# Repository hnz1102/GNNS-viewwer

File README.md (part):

<div align="center">
  <h1><code>GNSS Satellite Viewer</code></h1>
  
</div>

ESP32-S3 firmware for a handheld GNSS receiver display built around a u-blox
**MAX-F10S** module.  It decodes the receiver's NMEA output and shows the fix,
satellite constellation, a live map and recorded tracks on a 320×240 colour TFT,
and serves the same data over Wi-Fi to a browser.  Written in
Rust (esp-idf-hal / esp-idf-svc) with a C component (wolfSSH) for an SSH
console to the receiver.

## Features

| Feature | Description |
|---------|-------------|
| GNSS status | Fix quality, position, altitude, speed, course, HDOP/VDOP, satellites used/in view, UTC time (GPS, Galileo, BeiDou, GLONASS, QZSS, NavIC as supported by the receiver) |
| Sky view | Polar plot of every tracked satellite by azimuth/elevation, coloured by constellation, with an SNR bar chart |
| Live map | Google Maps Static API tile (satellite or roadmap) centred on the current fix, with a position trail, crosshair and scale bar |
| Offline map cache | Every downloaded tile is cached on eMMC; the nearest cached tile is shown when Wi-Fi or the API key is unavailable |
| Track log | Fixes are logged to a daily CSV on eMMC and can be browsed and replayed on the map (see [Track playback](#track-playback)) |
| Reverse geocoding | Street address for the current position via OpenStreetMap Nominatim |
| Earthquakes / EEW | Optional (`quake_enable`): recent earthquakes and emergency earthquake warnings from P2P地震情報, shown on a TFT page, plotted on the map and listed in the Web UI (see [Earthquakes and EEW](#earthquakes-and-eew-p2p地震情報)) |
| Time sync | System time from the GNSS receiver, plus NTP (up to 4 servers) |
| Web UI | Browser-based configuration, map, sky view, GNSS status and serial terminal |
| SSH console | Transparent SSH access to the receiver's serial port (`ssh … console com1`) |
| WPS | Wi-Fi Protected Setup (PBC mode) via `cfg.toml` or the Web UI |
| UDP Syslog | RFC 5424 remote logging over UDP |
| NVS settings | Persistent configuration stored in NVS; editable via the Web UI at runtime |

---

## Hardware

The reference hardware is a custom board; the KiCad design files and
production data (BOM, placement, netlist) are in [`hw/`](hw/).

| Part | Notes |
|------|-------|
| MCU | ESP32-S3 with 16 MB flash and octal PSRAM |
| GNSS receiver | u-blox MAX-F10S on UART1 (COM1), 9600 baud default |
| Display | ST7789V 320×240 SPI TFT |
| Storage | **64 GB eMMC** on the 8-bit SDMMC bus, mounted at `/emmc` (map tile cache and track log) |
| Battery | **LiPo, 1100 mAh**, on a JST-PH 2-pin connector; MCP73831 charge controller on board.  Voltage is read on GPIO13 (see `adc_conversion_factor`) |
| 1PPS output | **Internal** 1PPS (time-pulse) output port from the MAX-F10S TIMEPULSE1 pin.  1 Hz by default; the frequency (disabled, 1 Hz … 10 MHz) is set under *GPS TIMEPULSE* in the Web UI configuration page, saved in NVS and re-applied to the receiver at every boot |
| RTC | 32.768 kHz crystal on GPIO15/16 |
| Buttons | BOOT (GPIO0) plus three user buttons (GPIO4/5/6) |

### Enclosure

The 3D-printable enclosure is in [`STL/`](STL/):

| File | Content |
|------|---------|
| [`upper.stl`](STL/upper.stl) | Upper case |
| [`bottom.stl`](STL/bottom.stl) | Bottom case |
| [`button.stl`](STL/button.stl) | Button |
| [`sw-cover.stl`](STL/sw-cover.stl) | Switch cover |
| [`GNSS-VIEWER.f3d`](STL/GNSS-VIEWER.f3d) | Fusion 360 design data (source of the STL files; open it in Autodesk Fusion to modify the enclosure and re-export) |

### Pin assignment

| Function | GPIO |
|----------|------|
| GNSS UART1 TX / RX | 42 / 41 (`com1_tx_pin` / `com1_rx_pin`) |
| TFT SCLK / MOSI / CS / DC / RST | 48 / 45 / 40 / 39 / 38 |
| eMMC CLK / CMD | 46 / 3 |
| eMMC D0–D7 | 47, 21, 10, 9, 17, 18, 8, 7 |
| Battery voltage (ADC) | 13 |
| Power-source detect | 1 (high = DC jack, low = USB) |
| Buttons | 0 (BOOT/Page), 4 (+), 5 (−), 6 (MAP mode) |

---

## Display Pages

The BOOT button cycles through the pages in this order:

| # | Page | Content |
|---|------|---------|
| 1 | GNSS | Fix info, position, location name and satellite SNR bar chart |
| 2 | SKY VIEW | Polar satellite plot and per-satellite panel |
| 3 | MAP | Live map with trail, or the track being replayed |
| 4 | SAVED TRACKS | List of recorded tracks |
| 5 | SERIAL [COM1] | Raw terminal view of the receiver's serial stream |
| 6 | SYSTEM INFO | IP address, SSID, RSSI, battery voltage, chip temperature, free heap, serial settings, firmware version and build date/time |
| 7 | EARTHQUAKE | Recent earthquakes (only with `quake_enable = "true"`) |

### Buttons

The button hint at the bottom of the MAP, SAVED TRACKS and EARTHQUAKE pages uses
the same symbols everywhere:

| GPIO | On-screen legend | Short press | Hold |
|------|------------------|-------------|------|
| 0 (BOOT) | yellow ● `PAGE` (`EXIT` during track playback or an alert) | Next page — or end track playback | ≥ 10 s: factory reset |
| 4 | blue `+UP` | Context dependent (below) | Auto-repeat |
| 5 | blue `-DOWN` | Context dependent (below) | Auto-repeat |
| 6 | red ● `TYPE` / `PLAY` / `MAP` | Toggle satellite ↔ roadmap (`TYPE`) — start playback on the track list (`PLAY`) — show the highlighted epicenter on the quake page (`MAP`) | — |

GPIO4/5 act as follows:

| Where | GPIO4 (UP, +) / GPIO5 (DOWN, −) |
|-------|----------------------|
| MAP page, live | Zoom in / out |
| MAP page, track playback | Next / previous point (×10 once the button auto-repeats) |
| SAVED TRACKS page | Move the highlight up / down |
| EARTHQUAKE page | Move the highlight up / down |

Buttons are debounced at 50 ms; auto-repeat starts after 400 ms and repeats
every 300 ms.

**Factory reset** — hold BOOT for 10 s.  From 6 s the display shows a
"FACTORY RESET" countdown; at 10 s it erases NVS, restores the `cfg.toml`
defaults and reboots.

### TFT screenshots

Samples of every page, rendered at 2× with synthetic data (Tokyo Tower area,
made-up satellites and earthquakes) and real Google Static Maps tiles.  They
are generated by [`tools/screenshots`](tools/screenshots/) — see
[Regenerating the TFT screenshots](#regenerating-the-tft-screenshots).

| | |
|---|---|
| <br>**GNSS** | <br>**SKY VIEW** |
| <br>**MAP** (roadmap) | <br>**MAP** (satellite) |
| <br>**MAP**, zoom ≤ 5: ground point under each satellite | <br>**SAVED TRACKS** |
| <br>**TRACK PLAYBACK** | <br>**SERIAL [COM1]** |
| <br>**SYSTEM INFO** | <br>**EARTHQUAKE** |
| <br>**MAP** framed on the selected quake | <br>**NEW QUAKE** on the MAP |
| <br>**EEW** alert | <br>System message overlay |
| <br>**GNSS**, no fix | <br>**EARTHQUAKE**, waiting for data |

---

## Track Playback

While a fix is valid, the position is logged at most once every 5 s to
`/emmc/tracks/YYYY-MM-DD.csv` (UTC date, one file per day):

```
time_utc,lat,lon,alt_m,speed_kn,course_deg,fix_quality,num_sats,hdop
```

To replay a track:

1. Press **BOOT** until the **SAVED TRACKS** page is shown (newest date first).
2. Use **+ / −** to highlight a day and press **MAP mode** to start.
3. For the first 5 seconds the map is zoomed out to show the **whole route** (yellow
   line) and the **end point** (`E`).  It then returns to your normal tracking
   scale, starting at the first point.
4. **+ / −** step through the recorded points — hold the button to move ten at a
   time.  The info bar shows the date, point number, time, altitude and speed.
5. Press **BOOT** to end playback and return to the live map.

Tracks can be deleted from the Web UI (Storage section).

### Browsing tracks in the Web UI

Open **Tracks** from the configuration page (or `http://<device_ip>/tracks`).
Pick a day from the drop-down; the whole route (yellow) is shown first with its
start (`S`) and end (`E`).  Use ◀ ▶ / ⏮ ⏭ (±1 / ±10 points), the slider, or the
arrow keys (Shift = ±10) to move through the points, or **Play** to replay at
1–20 points per second.  **Overview** keeps the whole route in view; **Follow**
(selected automatically by Play and by the zoom buttons) centres on the current
point at the zoom you choose.

The viewer runs in the browser and is independent of the device: it does not
change what the LCD is showing, and the LCD's track playback does not affect it.
Like the Map page, it loads the map image straight from Google using the
`maps_api_key` (without a key the route is still drawn, on a plain background).

---

## Earthquakes and EEW (P2P地震情報)

With `quake_enable = "true"` in `cfg.toml` (default `"false"`) the unit shows
recent earthquakes and emergency earthquake warnings (緊急地震速報, EEW) from
[P2P地震情報](https://www.p2pquake.net/) (JSON API v2).  The data is
originally issued by the Japan Meteorological Agency (気象庁).  It needs Wi-Fi
and a synced clock (GNSS or NTP), because the connection is TLS.

| Where | What you get |
|-------|--------------|
| **EARTHQUAKE** page (TFT, page 7) | The 8 most recent events: time (JST), magnitude, maximum intensity (`I5-` = 5弱, `I5+` = 5強, …), depth and epicenter coordinates; tsunami warnings are flagged.  **+ / −** move the highlight, **MAP mode** (GPIO6) shows the highlighted epicenter on the MAP page |
| **MAP** page | Epicenters of recent earthquakes inside the visible map are drawn as circles — sized by magnitude, coloured by maximum intensity — with a label such as `M5.2 I5-` |
| **Web UI** (configuration page) | A *Recent Earthquakes* card with the epicenter name (Japanese), magnitude, intensity, depth and tsunami status.  The epicenter name opens the Web UI map (`/map?lat=…&lon=…&zoom=…`) centred on it |
| **EEW alert** | On a warning the TFT switches to the MAP page by itself and frames the epicenter **and this unit's own position** at the largest zoom that shows both: the epicenter is a large red `X`, joined to your position by a line, the header turns red (`!! EEW M6.3 I5- !!`) and the info bar shows magnitude, maximum forecast intensity, depth and the distance in km.  The Web UI shows a red banner with the forecast areas and a link to the same map view.  The alert stays up for 2 minutes, or until it is cancelled or **BOOT** is pressed |

The TFT font is ASCII only, so Japanese epicenter and area names appear in the
Web UI only; the TFT shows coordinates.  Without a GNSS fix the alert still
shows the epicenter, but cannot mark your position or give a distance.

How it works (`src/quake.rs`):

- A WebSocket (`wss://api.p2pquake.net/v2/ws`) receives the events as they are
  registered.  Warnings (code 556) raise the alert, earthquake reports (551) are
  merged into the list.  Test messages and warnings older than 3 minutes (by
  their issue time) are ignored, so a boot in the middle of an old event does
  not alert.
- REST (`/v2/history`) loads the initial list at boot, re-syncs it every
  30 minutes, and takes over — polling every 10 s (EEW) / 60 s (list) — while
  the WebSocket is down.
- **Memory:** the TLS WebSocket holds roughly 30 KB of internal RAM, which
  competes with the map tile download.  The WebSocket is therefore dropped for
  the duration of every map fetch and re-created once the map has been idle for
  about 12 s; any warning issued in the gap is recovered by a REST check right
  after it reconnects.  REST polling is skipped while internal RAM is low or a
  map fetch is running.  Watch *Free Heap (Internal)* in the Web UI and
  `[HEAP]` / `[WS]` / `[QUAKE]` in the log.
- The WebSocket needs the `esp_websocket_client` ESP-IDF component, pulled from
  the component registry at build time (declared in `Cargo.toml`), so the first
  build needs network access.

**Testing without a real earthquake.**  Build with the sandbox feature:

```bash
cargo build --release --features quake-sandbox
```

This points the feed at the P2P sandbox, which replays old data (including a
2023 Hokkaido EEW) and skips the "older than 3 minutes" check, so the whole
alert path fires right after boot.  Never ship a sandbox build.

> **Not a safety device.**  Delivery is not guaranteed and can be delayed; the
> warning only covers what the Meteorological Agency issues as a warning.  Do
> not rely on this unit for life-safety decisions.  Use the official channels.
> Use of the data is subject to the P2P地震情報
> [terms for secondary use](https://www.p2pquake.net/secondary_use/): credit the
> Japan Meteorological Agency and P2P地震情報 (the Web UI card already does).

---

## Architecture

```
u-blox MAX-F10S ──[UART1 / COM1]──► usb_host.rs (serial bridge)
                                      ├── gps_parser.rs ──► GPS state (fix, sats)
                                      │     ├── track_log.rs ─► /emmc/tracks/*.csv
                                      │     └── geocoder.rs ──► address lookup
                                      ├── serial_display.rs (TFT task) ──► display_pages.rs (page drawing)
                                      ├── WebSocket terminal  (/terminal)
                                      └── ssh_bridge.c (wolfSSH, port 22)

map_display.rs ── persistent fetch worker ──► Google Static Maps (HTTPS)
      │                                         └── map_cache.rs ─► /emmc/mapcache
      └── MAP page / Web UI (/map)

track_view.rs ── track list + playback state for the MAP / SAVED TRACKS pages

quake.rs ── WebSocket (EEW + events) + REST ──► p2pquake.net   (quake_enable)
      └── EARTHQUAKE page / MAP overlay / EEW alert / Web UI card
```

---

## Directory Layout

```
satellite-viewer/
├── src/
│   ├── main.rs           # Entry point, peripheral initialisation
│   ├── usb_host.rs       # COM1 UART bridge to the GNSS receiver + SSH bridge control
│   ├── gps_parser.rs     # NMEA / UBX parser, GPS state, time sync
│   ├── serial_display.rs # ST7789V display task (SPI init, redraw loop)
│   ├── display_pages.rs  # Page drawing (GNSS, sky view, map, track list, terminal, info, earthquake); no ESP-IDF dependency
│   ├── map_display.rs    # Map tile fetch, JPEG decode, zoom, position trail
│   ├── map_cache.rs      # eMMC tile cache index and eviction
│   ├── track_log.rs      # Daily CSV track logging
│   ├── track_view.rs     # Track list and playback state
│   ├── geocoder.rs       # Reverse geocoding (Nominatim)
│   ├── quake.rs          # Earthquake list + EEW (P2P地震情報 WebSocket / REST)
│   ├── emmc.rs           # eMMC (SDMMC 8-bit) mount
│   ├── httpserver.rs     # HTTP/WebSocket server, NVS config management
│   ├── wifi.rs           # Wi-Fi STA connection (DHCP / static IP) and WPS
│   ├── syslogger.rs      # UDP Syslog logger (RFC 5424)
│   ├── btn_ctrl.rs       # Button handling
│   ├── boot_log.rs       # NVS boot counter and rolling reset-reason log (last 10 entries)
│   └── gpio_ctrl.rs      # Shared GPIO state
├── components/
│   ├── ssh_bridge/       # SSH server C component (wolfSSH wrapper)
│   ├── wolfssh/          # wolfSSH (github.com/wolfSSL/wolfssh, commit 157cb01f)
│   └── wolfssl/          # wolfSSL/wolfCrypt (github.com/wolfSSL/wolfssl, commit b7e7e755)
├── tools/
│   └── screenshots/      # Host tool: renders every TFT page to PNG (see below)
├── docs/images/          # README images; tft/ holds the generated TFT screenshots
├── hw/                   # KiCad schematic/PCB and production files
├── STL/                  # Enclosure: STL files for 3D printing + Fusion 360 data (GNSS-VIEWER.f3d)
├── static/               # Embedded static files (xterm.js / css / fit addon)
├── cfg.toml              # Build-time default configuration (gitignored — contains credentials)
├── cfg.toml.tmp          # Template for cfg.toml (safe to commit)
├── sdkconfig.defaults    # ESP-IDF build settings
├── partitions.csv        # Flash partition table
├── setup_components.sh   # Initial setup script for components/
├── setup_env.sh          # One-shot environment setup (Rust, espup, udev)
└── build-flash-images.sh # Build merged flash images (quake_enable off / on) from the cfg.toml.tmp defaults
```

---

## Configuration

### cfg.toml (build-time defaults)

`cfg.toml.tmp` is the only template.  Before building, copy it to `cfg.toml`
(which is not committed, since it holds your Wi-Fi credentials and API key):

```bash
cp cfg.toml.tmp cfg.toml
```

Then edit `cfg.toml` for your environment.  The table name must match the crate
name, `[satellite-viewer]`, or the values are ignored.  Hardware variants are
selected with the settings below rather than separate templates:

| Setting | Default | Change it when |
|---------|---------|----------------|
| `com1_tx_pin` / `com1_rx_pin` | `42` / `41` | The GNSS receiver is wired to other pins (XIAO ESP32S3: `43` / `44`) |
| `display_enable` | `"true"` | There is no ST7789V TFT |
| `emmc_enable` | `"true"` | This unit has no eMMC fitted |
| `quake_enable` | `"false"` | You want the recent-earthquake list and **EEW** (緊急地震速報, emergency earthquake warning) alerts from P2P地震情報.  Off by default: it keeps a TLS WebSocket open (~30 KB of internal RAM) and needs Wi-Fi plus a synced clock.  Read at boot only, so rebuild after changing it — see [Earthquakes and EEW](#earthquakes-and-eew-p2p地震情報) |

```toml
[satellite-viewer]
wps_enable     = "true"     # "true": use WPS PBC on next boot when SSID is empty
wifi_ssid      = ""         # your-ssid
wifi_psk       = ""         # your-password
ip_mode        = "dhcp"           # "dhcp" or "static"
ip_address     = "192.168.0.200"
subnet_mask    = "255.255.255.0"
gateway        = "192.168.0.1"
dns            = "1.1.1.1"

syslog_server    = "192.168.0.140:514"
syslog_enable    = "false"
syslog_host_name = "esp32s3"
syslog_app_name  = "satellite-viewer"

ssh_user     = "admin"
ssh_password = "sshpass"

com1_tx_pin = "42"
com1_rx_pin = "41"
com1_baud   = "9600"

display_enable = "true"
display_port   = "com1"    # "com1"

ntp_server1 = "time.aws.com"
ntp_server2 = "time.google.com"
ntp_server3 = "time.cloudflare.com"
ntp_server4 = "ntp.nict.jp"

adc_conversion_factor = "437.98"

emmc_enable          = "true"    # "false": this unit has no eMMC chip populated — skip mount, avoids the SDMMC-failure-induced reset

# P2P地震情報 (p2pquake.net) feed: recent earthquakes + emergency earthquake warnings (EEW).
# "true": enable. Default "false" — it keeps a TLS WebSocket open (~30 KB of internal RAM)
# and needs WiFi plus a synced clock. Data: JMA via P2P地震情報.
quake_enable         = "false"

# Google Maps Static API key — get one at https://console.cloud.google.com/ (enable "Maps Static API", see README).
# This is only the default: the key can also be entered in the Web UI (Config > Map Settings), which overrides it.
# Never commit a real key here; put it in your local, uncommitted cfg.toml, or leave it unset and use the Web UI.
maps_api_key = ""
```

Values in `cfg.toml` are compiled into the firmware as defaults.
After boot they can be overridden via the Web UI or direct NVS writes; NVS values take priority.

### Google Maps API key

The map pages (LCD and Web UI) download images from the **Maps Static API**, so
they need a Google Maps Platform API key.  Without `maps_api_key` the MAP page
can still display tiles already stored in the eMMC cache, but will not download
new ones.

**Where to get one**

1. Sign in to the [Google Cloud console](https://console.cloud.google.com/) and
   create (or select) a project.
2. Link a **billing account** to the project.  Maps Platform APIs require one,
   even though usage within the free monthly allowance is not charged — see the
   [Google Maps Platform pricing](https://mapsplatform.google.com/pricing/) page
   for the current allowance.
3. Open **APIs & Services → Library**, search for **Maps Static API** and click
   **Enable**.
4. Open **APIs & Services → Credentials**, click **Create credentials → API key**
   and copy the key.  Step-by-step instructions are in Google's
   [Maps Static API documentation](https://developers.google.com/maps/documentation/maps-static/get-api-key).
5. Enter the key in the Web UI: **Config page → Map Settings → Google Maps API
   Key**, then **Save**.  It takes effect immediately (no reboot) and is stored
   in NVS.  To have a key built in as the default instead (for a fresh or
   factory-reset device), set it in `cfg.toml` and rebuild:

   ```toml
   maps_api_key = "your-api-key"
   ```

**Notes**

- The key is stored in NVS and can be changed from the Web UI at any time.
  `maps_api_key` in `cfg.toml` is only the default, used until a key is saved
  and restored by a factory reset (saving an empty field also falls back to it).
- The Web UI map pages load images directly from Google in your browser, so the
  device hands the key to any logged-in browser (`/api/mapkey`).  Keep the
  device login password strong, and do not share firmware images built with your
  own key (`build-flash-images.sh` builds from `cfg.toml.tmp`, whose key is empty).
- In the Cloud console, restrict the key under **API restrictions** to the
  **Maps Static API** only, and set a budget alert or quota so a leaked key cannot
  run up a bill.  An application restriction (HTTP referrer / IP) is awkward here
  because requests come both from the device and from browsers on your LAN.
- `cfg.toml` is not committed.  Never put a real key in `cfg.toml.tmp`, which is
  the template that gets committed.  Because the Web UI can set the key, you can
  leave `cfg.toml` empty and keep the key out of the build entirely.

---

## Wi-Fi Setup with WPS

**WPS (Wi-Fi Protected Setup)** allows you to connect to a Wi-Fi network without manually entering the SSID and password. This device supports **WPS Push Button Configuration (PBC)** mode.

### Method 1: Using cfg.toml and Factory Reset (Recommended for initial setup)

If you don't have Wi-Fi credentials yet or want to reconfigure via WPS without Web UI access:

1. **Edit `cfg.toml` before building** (or rebuild the firmware):
   ```toml
   wifi_ssid      = ""           # Set to empty string
   wps_enable     = "true"       # Enable WPS mode on boot
   ```

2. **Flash the firmware** to the device

3. On boot, the device will automatically enter WPS mode and wait for you to **press the WPS button on your Wi-Fi router** (timeout: 2 minutes)

4. Upon successful WPS connection, the credentials are saved to NVS and the device reboots

**Alternative: Trigger WPS via Factory Reset**

If the device is already running with Wi-Fi configured but you want to switch to WPS:

1. **Edit `cfg.toml`** to set `wps_enable = "true"` and `wifi_ssid = ""`
2. **Rebuild and flash** the firmware
3. **Perform a Factory Reset**: Press and hold the BOOT button (GPIO 0) for **≥10 seconds**
4. The device will erase NVS, restore `cfg.toml` defaults, and reboot into WPS mode
5. **Press the WPS button on your Wi-Fi router** within 2 minutes

> **Note**: Web UI is not accessible until Wi-Fi is connected, so this method is essential for initial setup or when you lose Wi-Fi access.

### Method 2: Using the Web UI (when already connected to Wi-Fi)

1. Navigate to the configuration page at `http://<device_ip>/`
2. Find the **WPS** section
3. Click the **"Start WPS"** button
4. **Press the WPS button on your Wi-Fi router** within 2 minutes
5. The device will automatically receive and save the Wi-Fi credentials and reboot

### WPS Fallback

If WPS fails or times out, the device will revert to the previously configured Wi-Fi credentials (from `cfg.toml` or NVS).

### Notes

- WPS PBC mode is the only supported WPS method (PIN mode is not supported)
- After successful WPS configuration, the new credentials are saved to NVS and persist across reboots
- You can still manually configure Wi-Fi credentials via `cfg.toml` or the Web UI if WPS is not available on your router

---

## Environment Setup

Run `setup_env.sh` **once** on a fresh Ubuntu / Debian machine (or WSL2) before
building.  The script performs all steps below automatically.

```bash
bash setup_env.sh
```

After the script finishes, open a new terminal (or reload your shell config) so
the environment variables take effect:

```bash
source "$HOME/.cargo/env"
source ~/export-esp.sh
```

### What the script does

| Step | Action |
|------|--------|
| 1 | Install system packages via `apt` |
| 2 | Install Rust toolchain via `rustup` (skipped if already present) |
| 3 | Install `ldproxy`, `espup`, `cargo-espflash` via Cargo |
| 4 | Install & update the ESP32-S3 Xtensa toolchain via `espup` |
| 5 | Source `~/export-esp.sh` (generated by `espup`) |
| 6 | Add udev rule for ESP32 USB device (`303a:1001`) and reload rules |

> If you prefer to run the steps manually, expand the section below.

<details>
<summary>Manual setup steps</summary>

```bash
# 1. System packages
sudo apt update && sudo apt -y install \
    git python3 python3-pip gcc build-essential curl \
    pkg-config libudev-dev libtinfo5 clang libclang-dev \
    llvm-dev udev libssl-dev python3.10-venv

# 2. Rust
curl --proto '=https' --tlsv1.2 -sSf https://sh.rustup.rs | sh
# Select option 1 (default install), then:
source "$HOME/.cargo/env"

# 3. Cargo tools
cargo install ldproxy
cargo install espup
cargo install cargo-espflash

# 4. ESP32-S3 toolchain
espup install
espup update

# 5. Activate ESP environment (add to ~/.bashrc / ~/.zshrc for persistence)
. ~/export-esp.sh

# 6. udev rules
sudo sh -c 'echo "SUBSYSTEMS==\"usb\", ATTRS{idVendor}==\"303a\", ATTRS{idProduct}==\"1001\", MODE=\"0666\"" > /etc/udev/rules.d/99-esp32.rules'
sudo udevadm control --reload-rules
sudo udevadm trigger
```

</details>

---

## Build and Flash

### Prerequisites

- Rust toolchain: `esp` channel (selected automatically via `rust-toolchain.toml`)
- [espup](https://github.com/esp-rs/espup) — ESP32-S3 Xtensa toolchain
- [espflash](https://github.com/esp-rs/espflash)
- ESP-IDF v5.4.2 (fetched automatically by the build)

### Initial component setup

Run once after cloning, or after a clean wipe of `components/`:

```bash
cd esp32-s3/satellite-viewer
bash setup_components.sh
```

This clones wolfssh and wolfssl at the verified commits, places the
ESP-IDF-specific `CMakeLists.txt` and `include/user_settings.h` on top, and
patches the FAT filesystem configuration to enable exFAT for the eMMC.

### Build

```bash
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
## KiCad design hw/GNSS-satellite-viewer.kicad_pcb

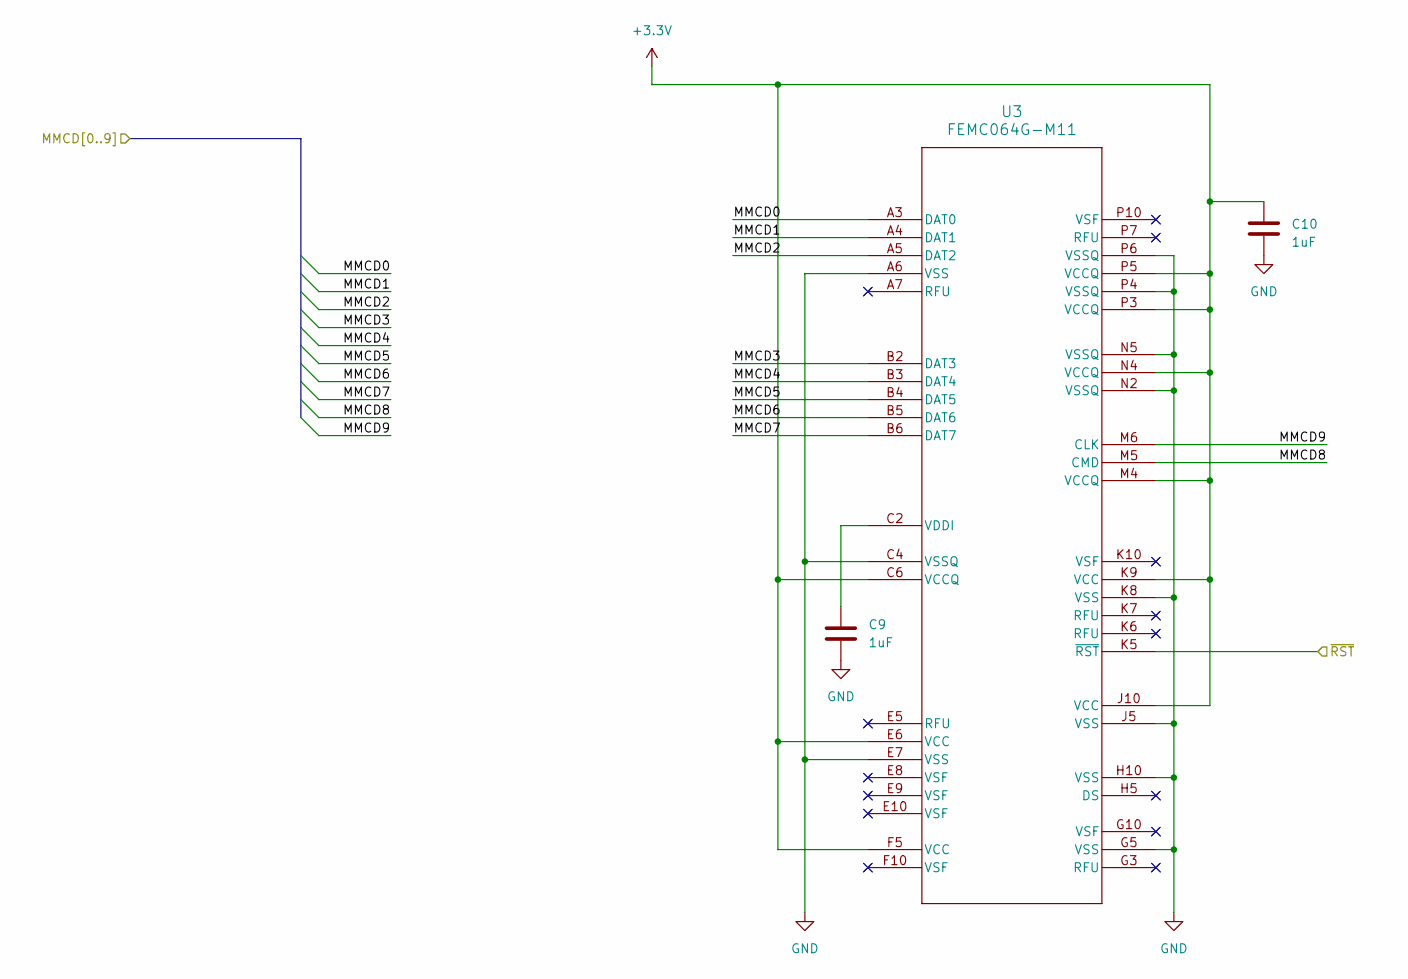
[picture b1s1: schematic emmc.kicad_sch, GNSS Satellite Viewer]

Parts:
C9, C10: 1uF; C_0805_2012Metric; digikey 1276-1026-1-ND
U3: FEMC064G-M11; EM32VSUKN FPGA153; digikey 3052-FEMC064G-M11-ND

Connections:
+3.3V: C10.1, U3.C6 (VCCQ), U3.E6 (VCC), U3.F5 (VCC), U3.J10 (VCC), U3.K9 (VCC), U3.M4 (VCCQ), U3.N4 (VCCQ), U3.P3 (VCCQ), U3.P5 (VCCQ); also elsewhere on the board
/MPU/MMCD0: U3.A3 (DAT0); also elsewhere on the board
/MPU/MMCD1: U3.A4 (DAT1); also elsewhere on the board
/MPU/MMCD2: U3.A5 (DAT2); also elsewhere on the board
/MPU/MMCD3: U3.B2 (DAT3); also elsewhere on the board
/MPU/MMCD4: U3.B3 (DAT4); also elsewhere on the board
/MPU/MMCD5: U3.B4 (DAT5); also elsewhere on the board
/MPU/MMCD6: U3.B5 (DAT6); also elsewhere on the board
/MPU/MMCD7: U3.B6 (DAT7); also elsewhere on the board
/MPU/MMCD8: U3.M5 (CMD); also elsewhere on the board
/MPU/MMCD9: U3.M6 (CLK); also elsewhere on the board
/MPU/~RESET: U3.K5 (~RST); also elsewhere on the board
GND: C9.2, C10.2, U3.A6 (VSS), U3.C4 (VSSQ), U3.E7 (VSS), U3.G5 (VSS), U3.H10 (VSS), U3.J5 (VSS), U3.K8 (VSS), U3.N2 (VSSQ), U3.N5 (VSSQ), U3.P4 (VSSQ), U3.P6 (VSSQ); also elsewhere on the board
unnamed: C9.1, U3.C2 (VDDI)

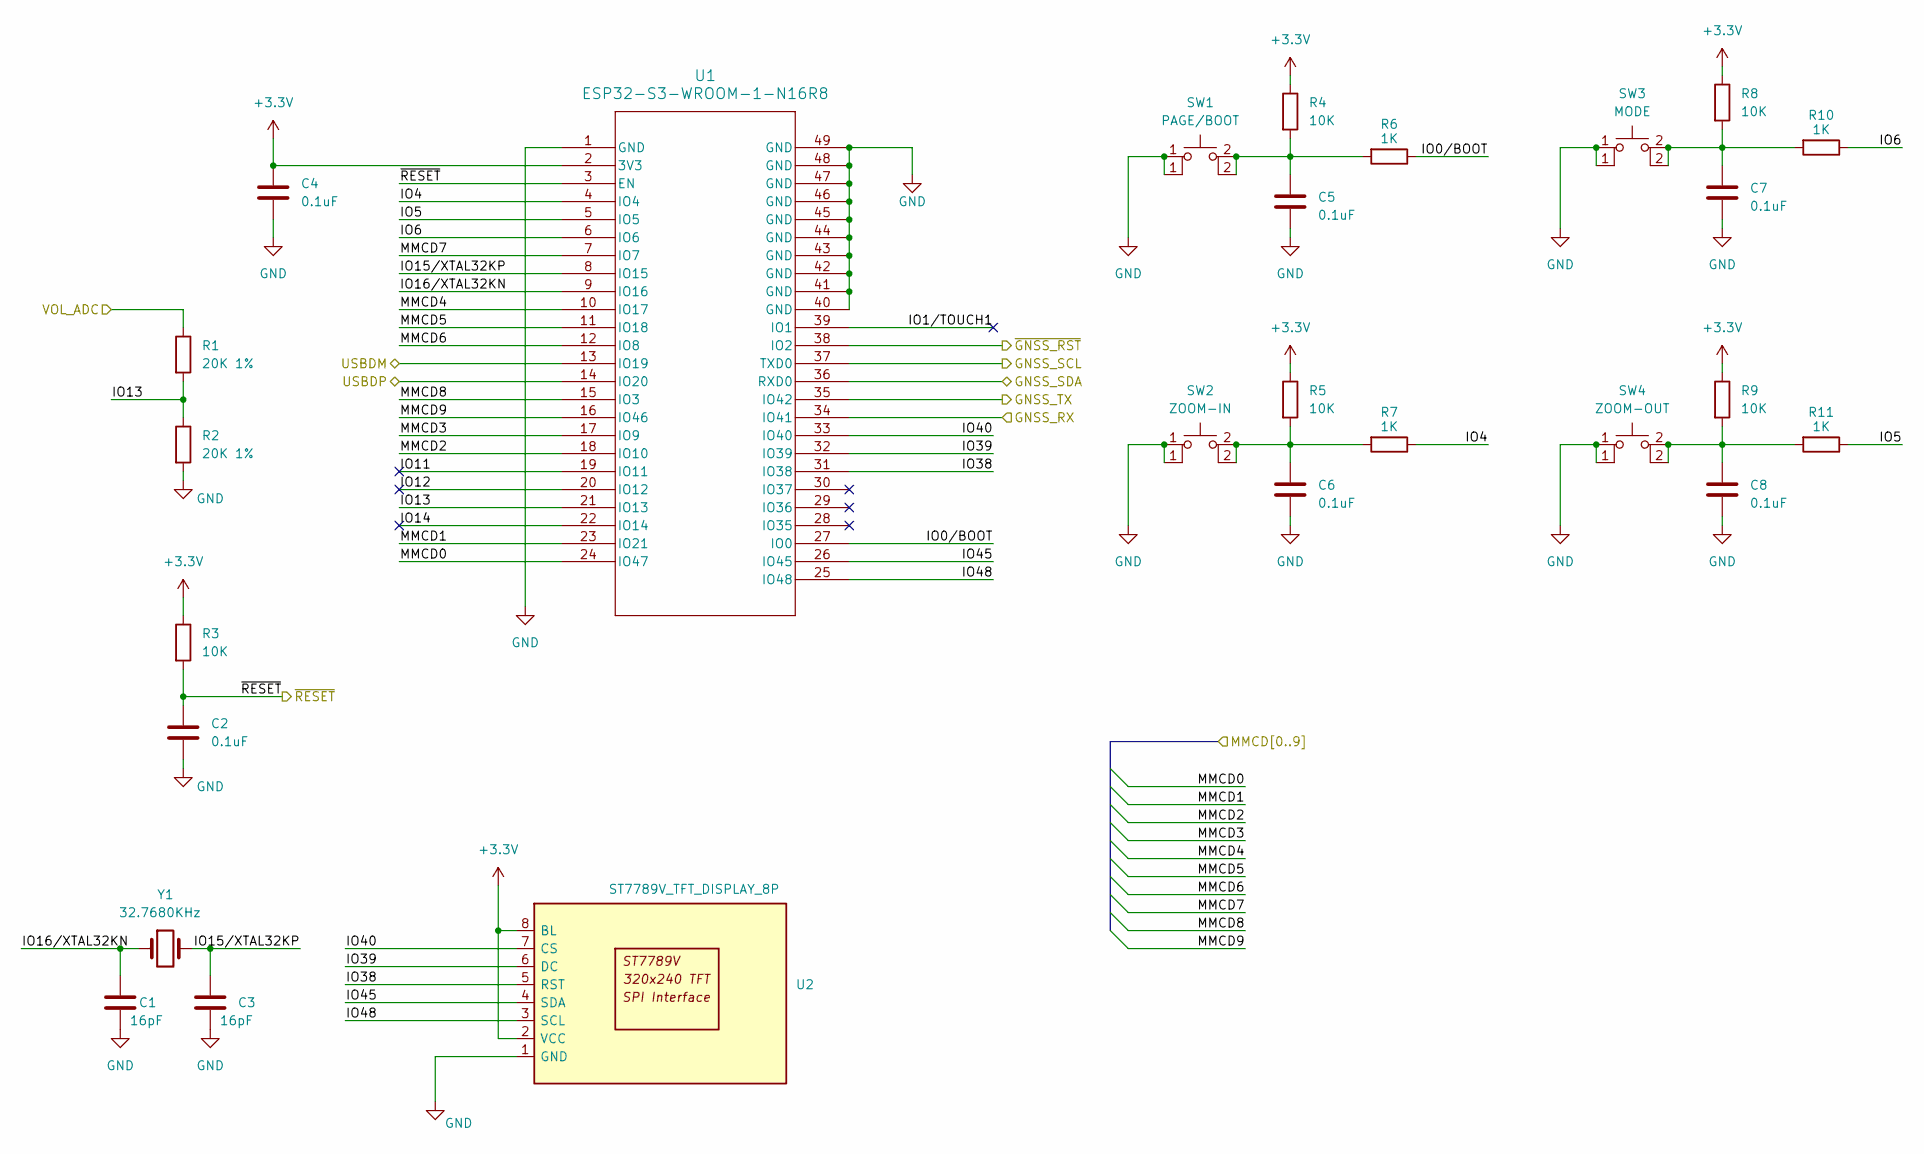
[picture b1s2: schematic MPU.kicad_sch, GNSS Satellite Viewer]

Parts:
C1, C3: 16pF; C_0603_1608Metric; digikey 1292-1490-1-ND
C2, C4, C5, C6, C7, C8: 0.1uF; C_0603_1608Metric; digikey 311-1344-1-ND
R1, R2: 20K 1%; R_0603_1608Metric; digikey 311-20.0KHRCT-ND
R3, R4, R5, R8, R9: 10K; R_0603_1608Metric; digikey 13-RC0603JR-1010KLCT-ND
R6, R7, R10, R11: 1K; R_0603_1608Metric; digikey 311-1.00KHRCT-ND
SW1: PAGE/BOOT; SW_PUSH_6mm_H8mm; digikey 2223-TS02-66-70-BK-160-LCR-D-ND
SW2: ZOOM-IN; SW_PUSH_6mm_H8mm; digikey 2223-TS02-66-70-BK-160-LCR-D-ND
SW3: MODE; SW_PUSH_6mm_H8mm; digikey 2223-TS02-66-70-BK-160-LCR-D-ND
SW4: ZOOM-OUT; SW_PUSH_6mm_H8mm; digikey 2223-TS02-66-70-BK-160-LCR-D-ND
U1: ESP32-S3-WROOM-1-N16R8; ESP32-S3-WROOM-1_EXP; digikey 1965-ESP32-S3-WROOM-1-N16R8CT-ND
U2: ST7789V_TFT_DISPLAY_8P; ST7789V TFT SPI DISPLAY 320x240 GMT020-02-8P; digikey GMT020-02-8P
Y1: 32.7680KHz; Crystal_SMD_3215-2Pin_3.2x1.5mm; digikey 2151-RT3215-32.768-12.5-TRCT-ND

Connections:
+3.3V: C4.1, R3.1, R4.1, R5.1, R8.1, R9.1, U1.2 (3V3), U2.2 (VCC), U2.8 (BL); also elsewhere on the board
/GNSS-RF/GNSS_RX: U1.35 (IO42); also elsewhere on the board
/GNSS-RF/GNSS_SCL: U1.37 (TXD0); also elsewhere on the board
/GNSS-RF/GNSS_SDA: U1.36 (RXD0); also elsewhere on the board
/GNSS-RF/GNSS_TX: U1.34 (IO41); also elsewhere on the board
/GNSS-RF/~GNSS_RST: U1.38 (IO2); also elsewhere on the board
/MPU/IO0/BOOT: R6.1, U1.27 (IO0)
/MPU/IO1/TOUCH1: U1.39 (IO1)
/MPU/IO4: R7.1, U1.4 (IO4)
/MPU/IO5: R11.1, U1.5 (IO5)
/MPU/IO6: R10.1, U1.6 (IO6)
/MPU/IO11: U1.19 (IO11)
/MPU/IO12: U1.20 (IO12)
/MPU/IO13: R1.2, R2.1, U1.21 (IO13)
/MPU/IO14: U1.22 (IO14)
/MPU/IO15/XTAL32KP: C3.1, U1.8 (IO15), Y1.2
/MPU/IO16/XTAL32KN: C1.1, U1.9 (IO16), Y1.1
/MPU/IO38: U1.31 (IO38), U2.5 (RST)
/MPU/IO39: U1.32 (IO39), U2.6 (DC)
/MPU/IO40: U1.33 (IO40), U2.7 (CS)
/MPU/IO45: U1.26 (IO45), U2.4 (SDA)
/MPU/IO48: U1.25 (IO48), U2.3 (SCL)
/MPU/MMCD0: U1.24 (IO47); also elsewhere on the board
/MPU/MMCD1: U1.23 (IO21); also elsewhere on the board
/MPU/MMCD2: U1.18 (IO10); also elsewhere on the board
/MPU/MMCD3: U1.17 (IO9); also elsewhere on the board
/MPU/MMCD4: U1.10 (IO17); also elsewhere on the board
/MPU/MMCD5: U1.11 (IO18); also elsewhere on the board
/MPU/MMCD6: U1.12 (IO8); also elsewhere on the board
/MPU/MMCD7: U1.7 (IO7); also elsewhere on the board
/MPU/MMCD8: U1.15 (IO3); also elsewhere on the board
/MPU/MMCD9: U1.16 (IO46); also elsewhere on the board
/MPU/USBDM: U1.13 (IO19); also elsewhere on the board
/MPU/USBDP: U1.14 (IO20); also elsewhere on the board
/MPU/~RESET: C2.1, R3.2, U1.3 (EN); also elsewhere on the board
/power/VOUT: R1.1; also elsewhere on the board
GND: C1.2, C2.2, C3.2, C4.2, C5.2, C6.2, C7.2, C8.2, R2.2, SW1.1, SW2.1, SW3.1, SW4.1, U1.1 (GND), U1.40 (GND), U1.41 (GND), U1.42 (GND), U1.43 (GND), U1.44 (GND), U1.45 (GND), U1.46 (GND), U1.47 (GND), U1.48 (GND), U1.49 (GND), U2.1 (GND); also elsewhere on the board
unnamed: C5.1, R4.2, R6.2, SW1.2
unnamed: C6.1, R5.2, R7.2, SW2.2
unnamed: C7.1, R8.2, R10.2, SW3.2
unnamed: C8.1, R9.2, R11.2, SW4.2

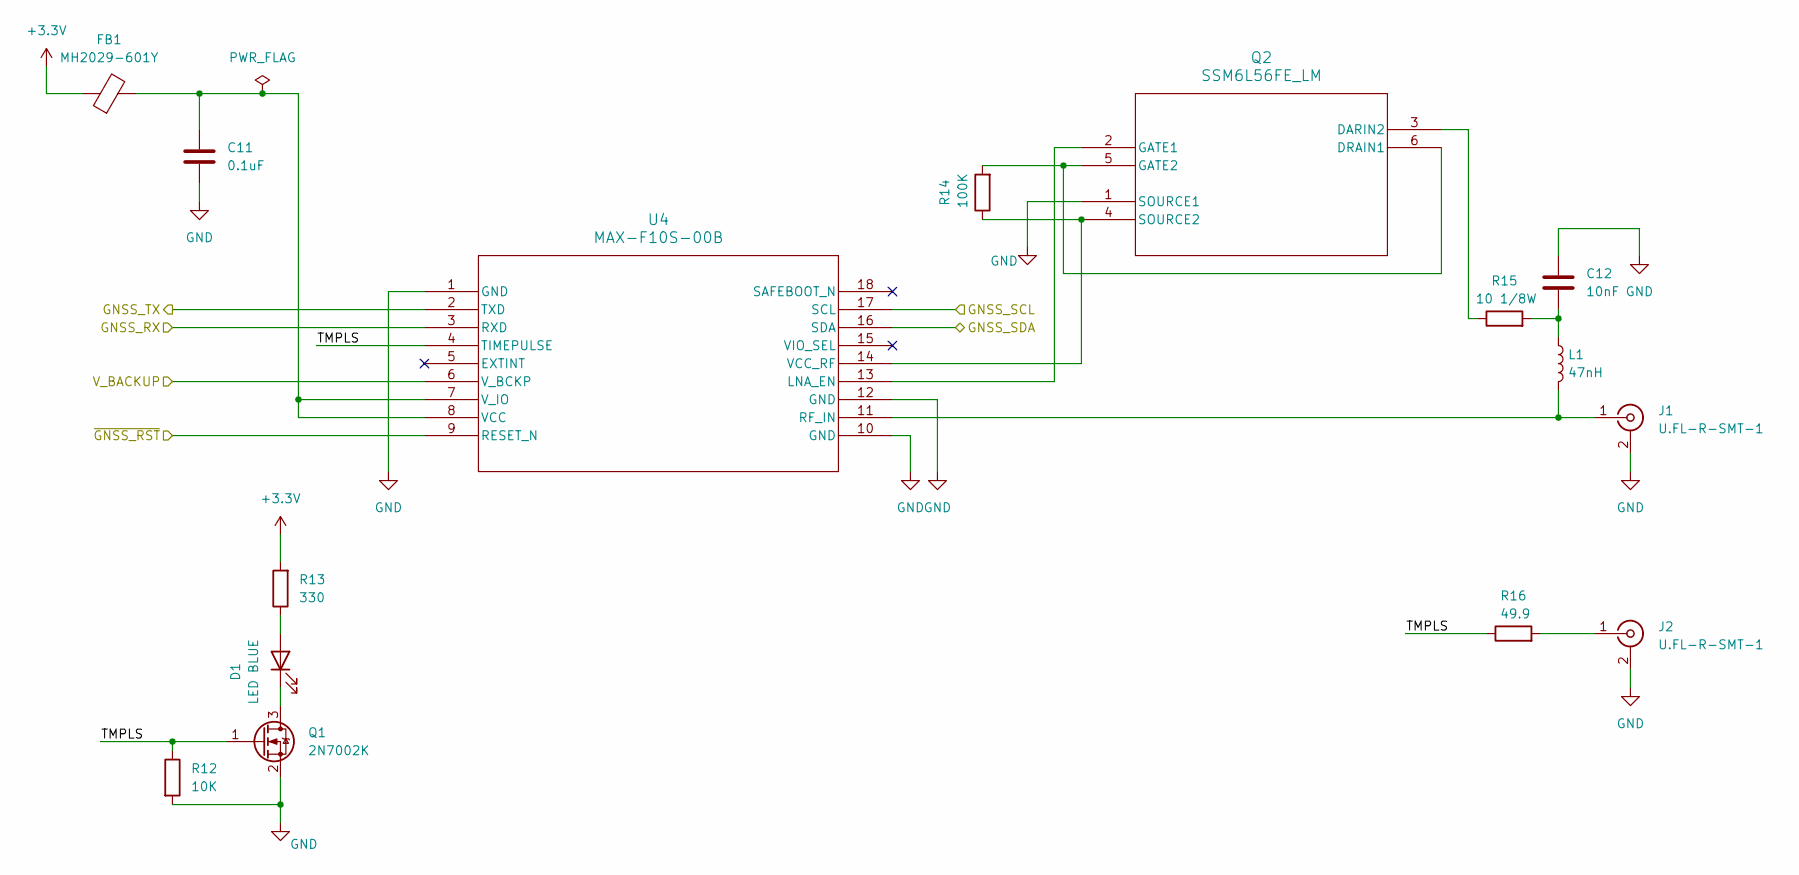
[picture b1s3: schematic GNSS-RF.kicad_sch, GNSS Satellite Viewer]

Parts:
C11: 0.1uF; C_0603_1608Metric; digikey 311-1344-1-ND
C12: 10nF; C_0603_1608Metric; digikey 311-1085-1-ND
D1: LED BLUE; LED_0603_1608Metric; digikey 3147-B1931NB--20C007614U1930CT-ND
FB1: MH2029-601Y; L_0805_2012Metric; digikey MH2029-601YCT-ND
J1, J2: U.FL-R-SMT-1; U.FL_Hirose_U.FL-R-SMT-1_Vertical; digikey 26-U.FL-R-SMT-1(80)CT-ND
L1: 47nH; L_0603_1608Metric; digikey 490-6582-1-ND
Q1: 2N7002K; SOT-23; digikey 5399-2N7002KCT-ND
Q2: SSM6L56FE_LM; SOT-563ES6_TOS; digikey 264-SSM6L56FELMCT-ND
R12: 10K; R_0603_1608Metric; digikey 13-RC0603JR-1010KLCT-ND
R13: 330; R_0603_1608Metric; digikey 13-RC0603JR-13330RLCT-ND
R14: 100K; R_0603_1608Metric; digikey 311-100KGRCT-ND
R15: 10 1/8W; R_0805_2012Metric; digikey 541-10.0CCT-ND
R16: 49.9; R_0603_1608Metric; digikey 311-49.9HRCT-ND
U4: MAX-F10S-00B; MAX-F10S_UBL; digikey 672-MAX-F10S-00BCT-ND

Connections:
+3.3V: FB1.1, R13.2; also elsewhere on the board
/GNSS-RF/GNSS_RX: U4.3 (RXD); also elsewhere on the board
/GNSS-RF/GNSS_SCL: U4.17 (SCL); also elsewhere on the board
/GNSS-RF/GNSS_SDA: U4.16 (SDA); also elsewhere on the board
/GNSS-RF/GNSS_TX: U4.2 (TXD); also elsewhere on the board
/GNSS-RF/TMPLS: Q1.1 (G), R12.1, R16.1, U4.4 (TIMEPULSE)
/GNSS-RF/V_BACKUP: U4.6 (V_BCKP); also elsewhere on the board
/GNSS-RF/~GNSS_RST: U4.9 (RESET_N); also elsewhere on the board
GND: C11.2, C12.1, J1.2 (Ext), J2.2 (Ext), Q1.2 (S), Q2.1 (SOURCE1), R12.2, U4.1 (GND), U4.10 (GND), U4.12 (GND); also elsewhere on the board
unnamed: C12.2, L1.1, R15.2
unnamed: D1.2 (A), R13.1
unnamed: D1.1 (K), Q1.3 (D)
unnamed: J1.1 (In), L1.2, U4.11 (RF_IN)
unnamed: J2.1 (In), R16.2
unnamed: Q2.3 (DARIN2), R15.1
unnamed: Q2.5 (GATE2), Q2.6 (DRAIN1), R14.2
unnamed: Q2.2 (GATE1), U4.13 (LNA_EN)
unnamed: Q2.4 (SOURCE2), R14.1, U4.14 (VCC_RF)
unnamed: C11.1, FB1.2, U4.7 (V_IO), U4.8 (VCC)

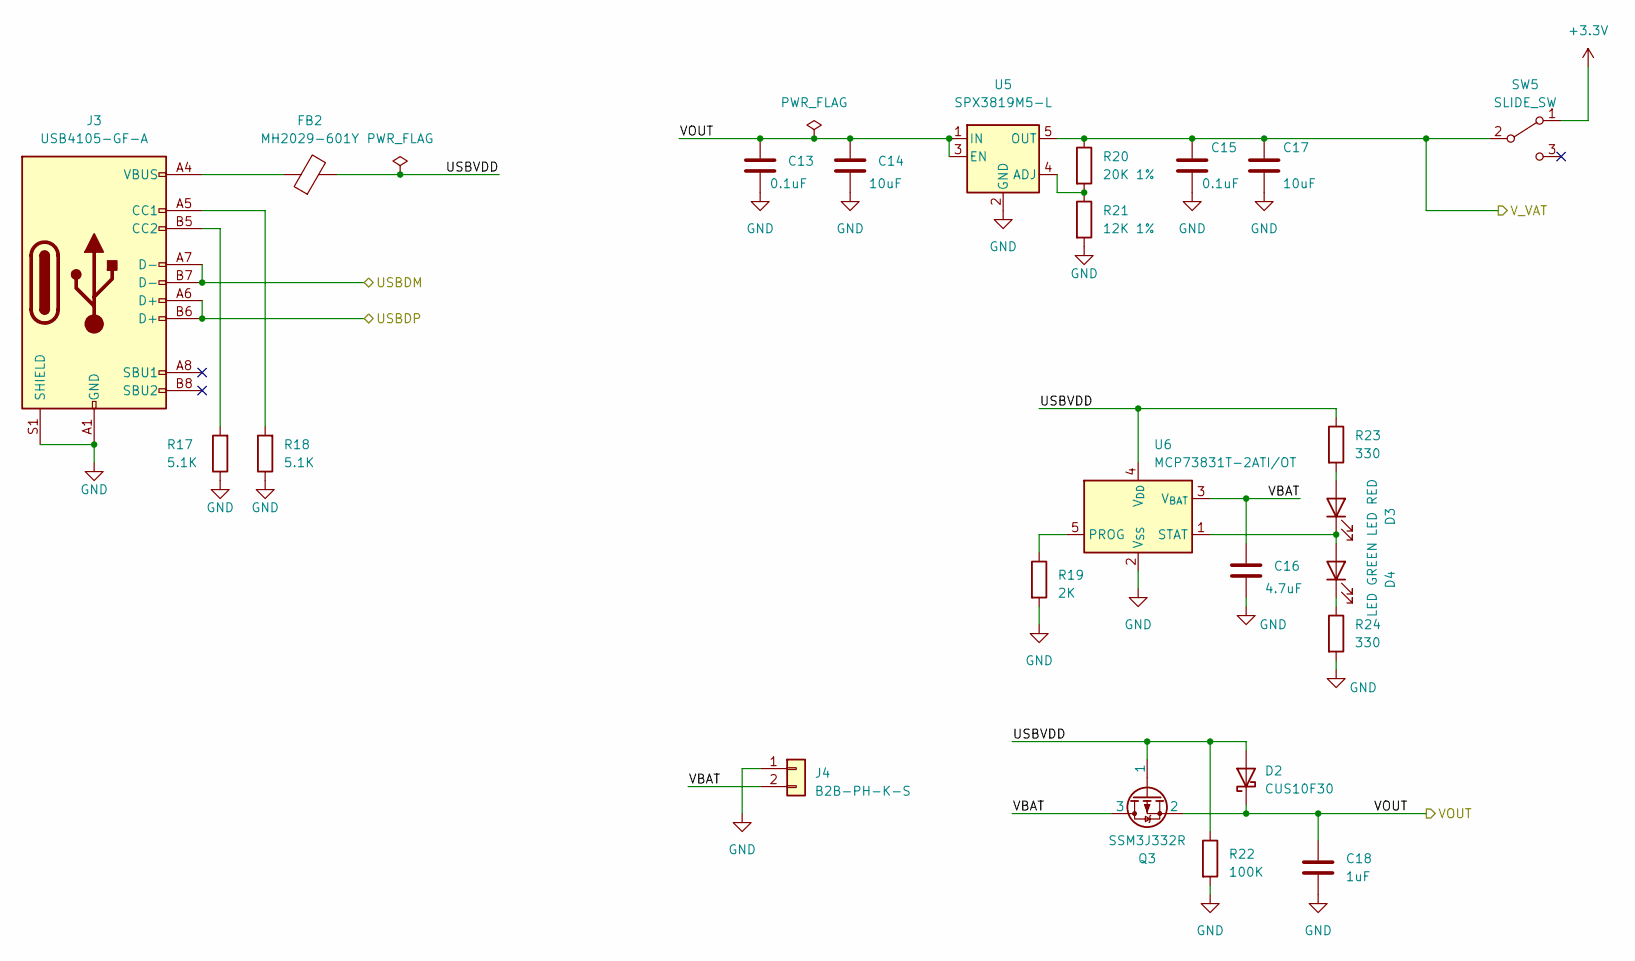
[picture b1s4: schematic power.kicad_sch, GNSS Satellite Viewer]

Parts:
C13, C15: 0.1uF; C_0603_1608Metric; digikey 311-1344-1-ND
C14, C17: 10uF; C_0805_2012Metric; digikey 1276-1096-1-ND
C16: 4.7uF; C_0805_2012Metric; digikey 1276-1244-1-ND
C18: 1uF; C_0805_2012Metric; digikey 1276-1026-1-ND
D2: CUS10F30; D_SOD-323; digikey CUS10F30H3FCT-ND
D3: LED RED; LED_0603_1608Metric; digikey 3147-B1931URO-20D000114U1930CT-ND
D4: LED GREEN; LED_0603_1608Metric; digikey 3147-B1911PG--20D000514U1930CT-ND
FB2: MH2029-601Y; L_0805_2012Metric; digikey MH2029-601YCT-ND
J3: USB4105-GF-A; USB_C_5077CR-16-SMC2-BK-TR; digikey 2073-USB4105-GF-ACT-ND
J4: B2B-PH-K-S; JST_PH_B2B-PH-K_1x02_P2.00mm_Vertical; digikey 455-1704-ND
Q3: SSM3J332R; SOT-23; digikey 4518-SSM3J332RCT-ND
R17, R18: 5.1K; R_0603_1608Metric; digikey 311-5.1KGRCT-ND
R19: 2K; R_0603_1608Metric; digikey 311-2.0KGRCT-ND
R20: 20K 1%; R_0603_1608Metric; digikey 311-20.0KHRCT-ND
R21: 12K 1%; R_0603_1608Metric; digikey 311-12.0KCRT-ND
R22: 100K; R_0603_1608Metric; digikey 311-100KGRCT-ND
R23, R24: 330; R_0603_1608Metric; digikey 13-RC0603JR-13330RLCT-ND
SW5: SLIDE_SW; SLIDE_SW_IS1235-G; digikey SLIDE_SW_IS1235-G https://akizukidenshi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
U5: SPX3819M5-L; SOT-23-5; digikey 1016-1871-1-ND
U6: MCP73831T-2ATI/OT; SOT-23-5; digikey MCP73831T-2ATI/OTCT-ND

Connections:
+3.3V: SW5.1 (A); also elsewhere on the board
/GNSS-RF/V_BACKUP: C15.1, C17.1, R20.1, SW5.2 (B), U5.5 (OUT); also elsewhere on the board
/MPU/USBDM: J3.A7 (D-), J3.B7 (D-); also elsewhere on the board
/MPU/USBDP: J3.A6 (D+), J3.B6 (D+); also elsewhere on the board
/power/USBVDD: D2.2 (A), FB2.2, Q3.1, R22.1, R23.1, U6.4 (V_{DD})
/power/VBAT: C16.1, J4.2, Q3.3, U6.3 (V_{BAT})
/power/VOUT: C13.1, C14.1, C18.1, D2.1 (K), Q3.2, U5.1 (IN), U5.3 (EN); also elsewhere on the board
GND: C13.2, C14.2, C15.2, C16.2, C17.2, C18.2, J3.A1 (GND), J3.A12 (GND), J3.B1 (GND), J3.B12 (GND), J3.S1 (SHIELD), J4.1, R17.1, R18.1, R19.2, R21.2, R22.2, R24.2, U5.2 (GND), U6.2 (V_{SS}); also elsewhere on the board
unnamed: D3.2 (A), R23.2
unnamed: D3.1 (K), D4.2 (A), U6.1 (STAT)
unnamed: D4.1 (K), R24.1
unnamed: FB2.1, J3.A4 (VBUS), J3.A9 (VBUS), J3.B4 (VBUS), J3.B9 (VBUS)
unnamed: J3.A5 (CC1), R18.2
unnamed: J3.B5 (CC2), R17.2
unnamed: R20.2, R21.1, U5.4 (ADJ)
unnamed: R19.1, U6.5 (PROG)

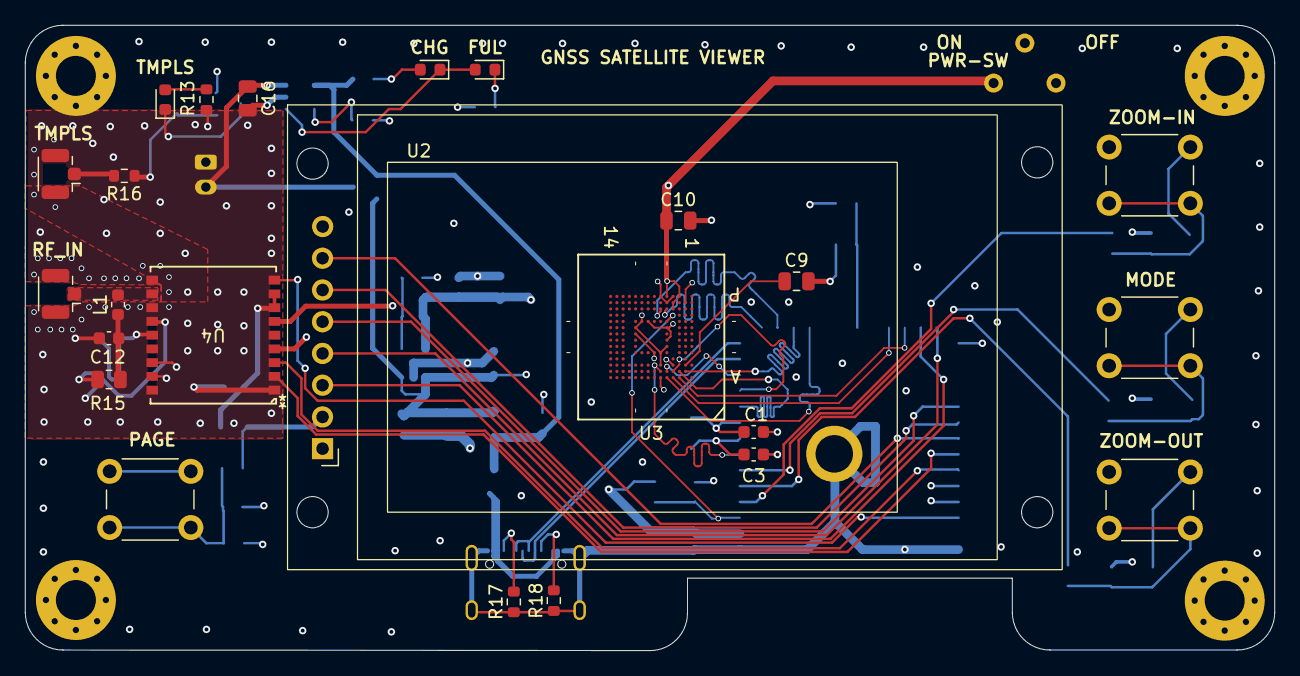
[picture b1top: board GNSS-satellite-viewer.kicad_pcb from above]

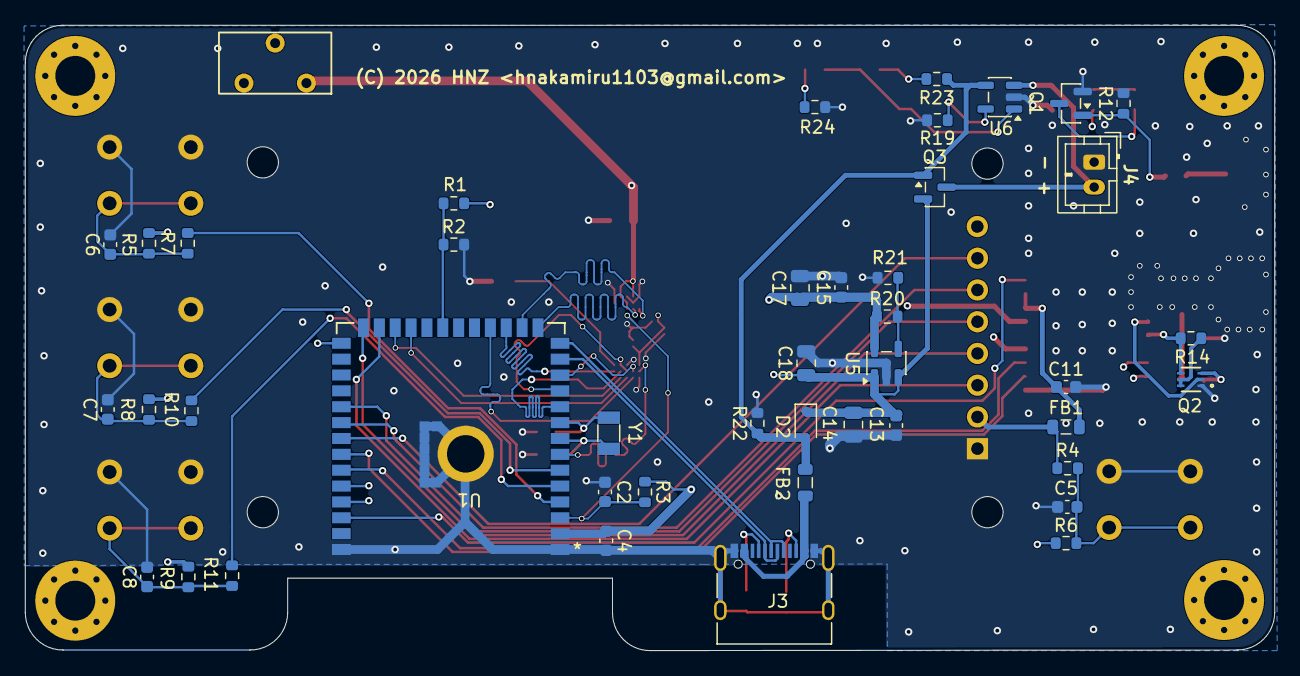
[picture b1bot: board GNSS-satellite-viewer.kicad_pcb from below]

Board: 4 copper layers, 100.0 x 50.0 mm, 68 parts (44 on the bottom side), 60 nets.

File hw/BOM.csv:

"Reference","Qty","Value","DNP","Footprint","digikey/other"
"C1,C3","2","16pF","","Capacitor_SMD:C_0603_1608Metric","1292-1490-1-ND"
"C2,C4,C5,C6,C7,C8,C11,C13,C15","9","0.1uF","","Capacitor_SMD:C_0603_1608Metric","311-1344-1-ND"
"C9,C10,C18","3","1uF","","Capacitor_SMD:C_0805_2012Metric","1276-1026-1-ND"
"C12","1","10nF","","Capacitor_SMD:C_0603_1608Metric","311-1085-1-ND"
"C14,C17","2","10uF","","Capacitor_SMD:C_0805_2012Metric","1276-1096-1-ND"
"C16","1","4.7uF","","Capacitor_SMD:C_0805_2012Metric","1276-1244-1-ND"
"D1","1","LED BLUE","","LED_SMD:LED_0603_1608Metric","3147-B1931NB--20C007614U1930CT-ND"
"D2","1","CUS10F30","","Diode_SMD:D_SOD-323","CUS10F30H3FCT-ND"
"D3","1","LED RED","","LED_SMD:LED_0603_1608Metric","3147-B1931URO-20D000114U1930CT-ND"
"D4","1","LED GREEN","","LED_SMD:LED_0603_1608Metric","3147-B1911PG--20D000514U1930CT-ND"
"FB1,FB2","2","MH2029-601Y","","Inductor_SMD:L_0805_2012Metric","MH2029-601YCT-ND"
"J1,J2","2","U.FL-R-SMT-1","","Connector_Coaxial:U.FL_Hirose_U.FL-R-SMT-1_Vertical","26-U.FL-R-SMT-1(80)CT-ND"
"J3","1","USB4105-GF-A","","Library:USB_C_5077CR-16-SMC2-BK-TR","2073-USB4105-GF-ACT-ND"
"J4","1","B2B-PH-K-S","","Connector_JST:JST_PH_B2B-PH-K_1x02_P2.00mm_Vertical","455-1704-ND"
"L1","1","47nH","","Inductor_SMD:L_0603_1608Metric","490-6582-1-ND"
"Q1","1","2N7002K","","Package_TO_SOT_SMD:SOT-23","5399-2N7002KCT-ND"
"Q2","1","SSM6L56FE_LM","","Library:SOT-563ES6_TOS","264-SSM6L56FELMCT-ND"
"Q3","1","SSM3J332R","","Package_TO_SOT_SMD:SOT-23","4518-SSM3J332RCT-ND"
"R1,R2,R20","3","20K 1%","","Resistor_SMD:R_0603_1608Metric","311-20.0KHRCT-ND"
"R3,R4,R5,R8,R9,R12","6","10K","","Resistor_SMD:R_0603_1608Metric","13-RC0603JR-1010KLCT-ND"
"R6,R7,R10,R11","4","1K","","Resistor_SMD:R_0603_1608Metric","311-1.00KHRCT-ND"
"R13,R23,R24","3","330","","Resistor_SMD:R_0603_1608Metric","13-RC0603JR-13330RLCT-ND"
"R14,R22","2","100K","","Resistor_SMD:R_0603_1608Metric","311-100KGRCT-ND"
"R15","1","10 1/8W","","Resistor_SMD:R_0805_2012Metric","541-10.0CCT-ND"
"R16","1","49.9","","Resistor_SMD:R_0603_1608Metric","311-49.9HRCT-ND"
"R17,R18","2","5.1K","","Resistor_SMD:R_0603_1608Metric","311-5.1KGRCT-ND"
"R19","1","2K","","Resistor_SMD:R_0603_1608Metric","311-2.0KGRCT-ND"
"R21","1","12K 1%","","Resistor_SMD:R_0603_1608Metric","311-12.0KCRT-ND"
"SW1","1","PAGE/BOOT","","Button_Switch_THT:SW_PUSH_6mm_H8mm","2223-TS02-66-70-BK-160-LCR-D-ND"
"SW2","1","ZOOM-IN","","Button_Switch_THT:SW_PUSH_6mm_H8mm","2223-TS02-66-70-BK-160-LCR-D-ND"
"SW3","1","MODE","","Button_Switch_THT:SW_PUSH_6mm_H8mm","2223-TS02-66-70-BK-160-LCR-D-ND"
"SW4","1","ZOOM-OUT","","Button_Switch_THT:SW_PUSH_6mm_H8mm","2223-TS02-66-70-BK-160-LCR-D-ND"
"SW5","1","SLIDE_SW","","Library:SLIDE_SW_IS1235-G","SLIDE_SW_IS1235-G  https://akizukidenshi.com/catalog/g/g115368/"
"U1","1","ESP32-S3-WROOM-1-N16R8","","Library:ESP32-S3-WROOM-1_EXP","1965-ESP32-S3-WROOM-1-N16R8CT-ND"
"U2","1","ST7789V_TFT_DISPLAY_8P","","Library:ST7789V TFT SPI DISPLAY 320x240 GMT020-02-8P","GMT020-02-8P"
"U3","1","FEMC064G-M11","","Library:EM32VSUKN FPGA153","3052-FEMC064G-M11-ND"
"U4","1","MAX-F10S-00B","","Library:MAX-F10S_UBL","672-MAX-F10S-00BCT-ND"
"U5","1","SPX3819M5-L","","Package_TO_SOT_SMD:SOT-23-5","1016-1871-1-ND"
"U6","1","MCP73831T-2ATI/OT","","Package_TO_SOT_SMD:SOT-23-5","MCP73831T-2ATI/OTCT-ND"
"Y1","1","32.7680KHz","","Crystal:Crystal_SMD_3215-2Pin_3.2x1.5mm","2151-RT3215-32.768-12.5-TRCT-ND"

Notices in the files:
README.md:
**wolfSSH** | commit `157cb01f` | GPLv3 (or commercial) | SSH server protocol
**wolfSSL / wolfCrypt** | commit `b7e7e755` | GPLv3 (or commercial) | Cryptography library
> **Note on wolfSSH / wolfSSL licensing:
> Both wolfSSH and wolfSSL are dual-licensed under **GPLv3** (open source) or a
hw/GNSS-RF.kicad_sch:
Licensed under CC-BY-SA V4.0
(C) 2026 Hiroshi Nakajima
hw/GNSS-satellite-viewer.kicad_pcb:
(C) 2026 HNZ
